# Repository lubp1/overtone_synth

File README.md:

This is a project to a composition with technological supports subject. The objective was to make an board with an Arduino to capture the data of five potentiometers and push buttons. Then, this data is send through the serial port, using the Open Sound Control protocol to PureData, an interactive programming language made for sound manipulation. The printed circuit board made can be found on the PCB directory, and the arduino firmware on the Firmware directory.

The PureData part was responsible for manipulating five senoidal oscillators. Using the potentiometers, one could change each oscillator's frequency, and with the push buttons turn then on and off. It also capture the input on the computer's soundboard, to apply digital effects (delay and reverb) to the performer's microphone. The PureData code can be found on the PD folder.

The artistic objective of this project was to mimic the sound of buzzers. The performer was a singer, who would sing near the frequencies of the oscillators, making beats, similar to those made by the buzzers.

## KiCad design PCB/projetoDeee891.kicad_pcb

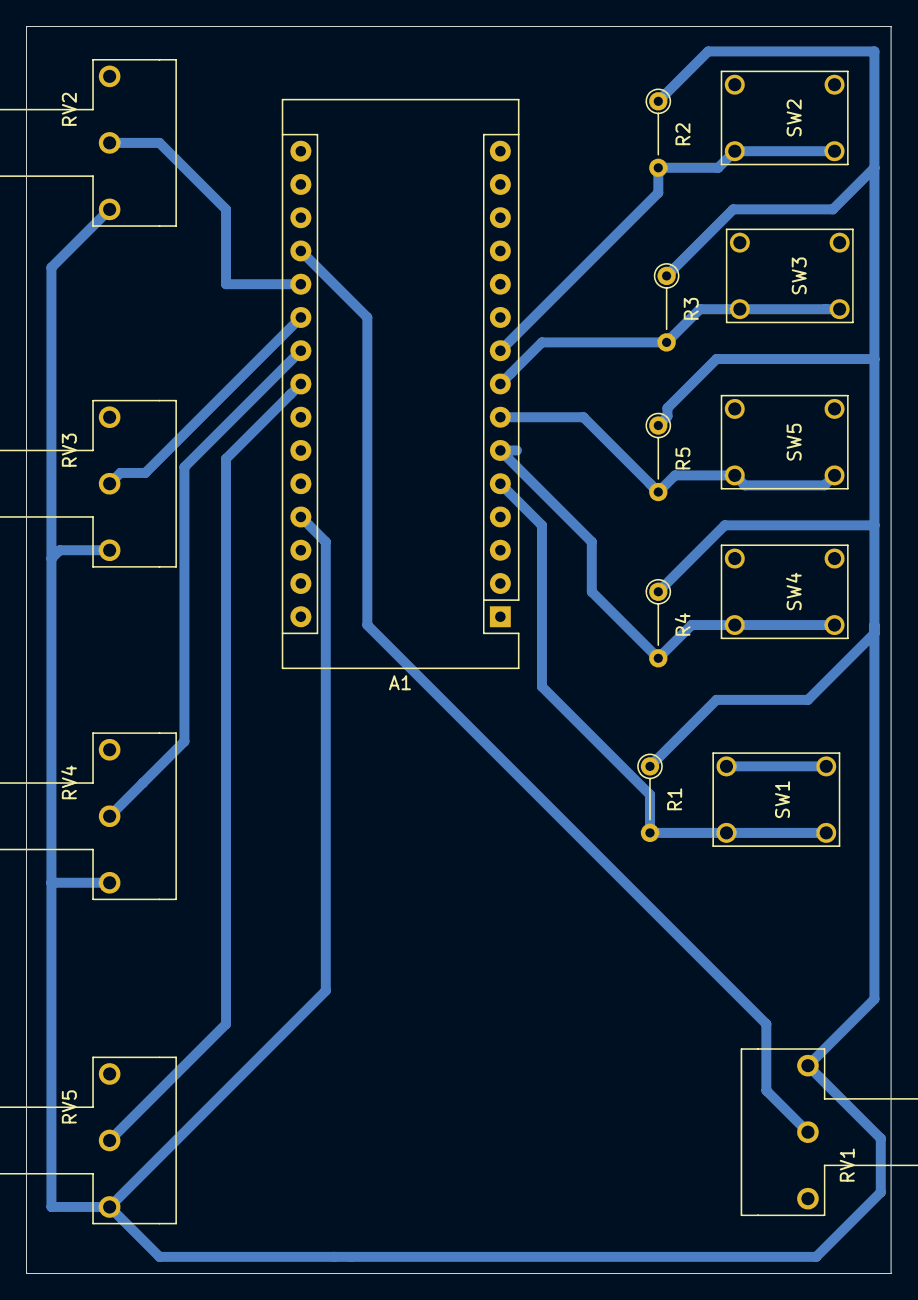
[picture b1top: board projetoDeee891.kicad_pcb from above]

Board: 2 copper layers, 66.0 x 95.3 mm, 16 parts (0 on the bottom side), 12 nets.

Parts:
A1: Arduino_Nano_v3.x; Arduino_Nano
R1, R2, R3, R4, R5: 10k; R_Axial_DIN0204_L3.6mm_D1.6mm_P5.08mm_Vertical
RV1, RV2, RV3, RV4, RV5: R_POT; Potentiometer_Sideways
SW1, SW2, SW3, SW4, SW5: SW_Push; PushButton

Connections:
GND: A1.4, A1.29, RV1.1, RV2.1, RV3.1, RV4.1, RV5.1, SW1.2, SW2.2, SW3.2, SW4.2, SW5.2
unnamed: A1.5, R1.2, SW1.1
unnamed: A1.6, R4.2, SW4.1
unnamed: A1.7, R5.2, SW5.1
unnamed: A1.8, R3.2, SW3.1
unnamed: A1.9, R2.2, SW2.1
unnamed: A1.19, RV1.2
unnamed: A1.20, RV2.2
unnamed: A1.21, RV3.2
unnamed: A1.22, RV4.2
unnamed: A1.23, RV5.2
unnamed: A1.27, R1.1, R2.1, R3.1, R4.1, R5.1, RV1.3, RV2.3, RV3.3, RV4.3, RV5.3

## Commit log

2020-05-24 Adding firmware, pcb and puredata codes
